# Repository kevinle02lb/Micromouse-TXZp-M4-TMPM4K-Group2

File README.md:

<div align="center">

# 🐭 Toshiba Micromouse

**Autonomous 16×16 Maze-Solving Robot**  
*Register-level firmware on Arm Cortex-M4*

</div>

---

## Overview

Micromouse is a classic robotics competition: an autonomous palm-sized robot explores a 16×16 grid maze, maps the walls, & solves for the center.

This project implements the entire stack from scratch: custom 4-layer PCB, mechanical chassis, and register-level firmware, with no reliance on external HAL libraries.

---

## Platform

<div align="center">

### **Toshiba TMPM4KNF10AFG**, Arm Cortex-M4 with FPU

</div>

The TMPM4KNF10AFG comes from the **[M4K Group](https://toshiba.semicon-storage.com/us/semiconductor/product/microcontrollers/txz4aplus-series/m4k-group.html)** of Toshiba's **[TXZ+™4A Series](https://toshiba.semicon-storage.com/us/semiconductor/product/microcontrollers/txz4aplus-series.html)**, a line of 160 MHz Arm Cortex-M4 microcontrollers built for motor and inverter control. It pairs a fast floating-point core with dedicated on-chip hardware for driving motors, reading encoders, and sampling analog sensors. The same parts show up in BLDC/PMSM drives, HVAC compressors, power tools, and factory automation, and they carry IEC 60730 self-diagnosis support for appliance functional safety.

| Capability | Role in this build |
|-----------|--------------------|
| Cortex-M4 @ 160 MHz + FPU | Navigation, PID, and flood-fill maze solving |
| On-chip motor & encoder hardware | Wheel feedback and PPG-generated motor PWM |
| High-speed analog sensing | IR wall detection |

Here the same silicon runs a much smaller problem: a 1 kHz driven by an interrupt and closed-loop PID over two brushed DC gear-motors. Dedicated hardware handles encoder counting and motor PWM, so the CPU stays free for navigation and flood-fill maze solving.

---

## Built With

<div align="center">

|  |  |  |  |  |  |
|:---:|:---:|:---:|:---:|:---:|:---:|
| **Arm Cortex-M4** | **Keil µVision** | **KiCad** | **Fusion 360** | **Git** | **MATLAB** |
| Register-level C | IDE / Build / Flash | 4-layer PCB | Chassis CAD | Version Control | Data Analysis |

</div>

## Gallery

<div align="center">

 &nbsp;&nbsp;

*Custom PCB*

<br>

*(Outdated Version) Fusion 360 render of the full mechanical assembly*

</div>

---

## Documentation
 
| Path | Contents |
|------|----------|
| [`src/README.md`](src/README.md) | Firmware architecture, control loops, pin map, timer config |
| [`hardware/README.md`](hardware/README.md) | Hardware overview: chassis (Fusion) + PCB (KiCad) |
| [`hardware/pcb/README.md`](hardware/pcb/README.md) | Board specs, layout, schematic, component list |
| [`docs/README.md`](docs/README.md) | Docs index: assets, evidence, and analysis tooling |
| [`docs/evidence/README.md`](docs/evidence/README.md) | Module-test checklist and captured evidence |

---

## Quick Start

```text
IDE:     Keil µVision
Target:  TMPM4KNF10AFG (Arm Cortex-M4)
Debug:   CMSIS-DAP
Flash:   512 KB on-chip

```
[`Quick Start`](docs/README.md)

---

<div align="center">

**Kevin Le** &nbsp;•&nbsp; 2026 &nbsp;
</div>

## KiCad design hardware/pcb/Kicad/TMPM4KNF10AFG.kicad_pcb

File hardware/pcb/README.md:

<div align="center">

# Micromouse PCB

**Custom 4-Layer Control Board**  
*Integrated MCU, motor drivers, and IR sensing*

</div>

---

## Overview

The mainboard is a custom 4-layer PCB designed in KiCad that carries the full electronics stack on a single micromouse-sized board: the microcontroller, dual motor drivers, four IR wall sensors, and the power and debug interface.

---

## Board Specs

| Spec | Detail |
|------|--------|
| Layers | 4-layer |
| MCU | Toshiba TMPM4KNF10AFG (Cortex-M4F) |
| Motor drivers | 2 × TB67H450AFNG H-bridge |
| Sensing | 4 × IR emitter / receiver pairs |
| Debug | CMSIS-DAP (SWD) via TXB0104 level shifter |
| Battery | 3S LiPo, 11.1 V nominal |
| Logic supply | 5 V from a buck converter |

---

## Power

| Rail | Voltage | Source |
|------|---------|--------|
| Battery | 11.1 V (3S LiPo) | Pack |
| Motor | 11.1 V | Direct from pack |
| Logic | 5 V | Buck converter |

Motors are the 12 V variant, so they run straight off the pack. Buck rather than
LDO because 11.1 V down to 5 V is too big a drop to burn as heat.

---

## Layout

<div align="center">

*Copper layers and component placement*

</div>

---

## Key Components

| Component | Part | Role |
|-----------|------|------|
| MCU | TMPM4KNF10AFG | Cortex-M4F, control & sensing |
| Motor driver | TB67H450AFNG ×2 | Brushed DC H-bridge, PWM speed control |
| Motors | Pololu #5211 N20 30:1 | Drive, with quadrature encoders |
| IR sensing | IR LED + phototransistor ×4 | Wall detection via ADC |
| Level shifter | TXB0104 | 5 V ↔ 3.3 V for SWD debug |

---

## Bench Setup

External equipment used for programming and debug:

<div align="center">

 &nbsp;&nbsp; 

*SWD debug via level shifter, and USB-UART for serial logging*

</div>

| Equipment | Purpose |
|-----------|---------|
| CMSIS-DAP probe | SWD programming & debug |
| Logic level shifter | 5 V ↔ 3.3 V for the SWD lines |
| USB-UART converter | Serial console (115200 8-N-1) over the CH340G/debug UART |

Note: TXB0104 OE has a Pull-up. Recommended: 10k - 50k Ohms 

---

## Redesign Notes

Ideas for anyone rebuilding this board, roughly ordered by how much they save.

### Drop to 2 layers

The 4-layer stackup buys a solid ground plane and easy routing. A 2-layer board
runs about half the price at most fabs, and the component count here is low
enough to make it workable. Plan the ground pour carefully around the ADC inputs
if you do.

### Use a 64-pin MCU

The M4K group ships in packages from 64 to 100 pins. This build uses roughly
twenty. A smaller package costs less and frees board area, which is the other
half of shrinking the board.

### Remove the encoder pull-ups

The Pololu encoder board already pulls channels A and B to Vcc through 10 kΩ.
On-board pull-ups parallel those down to 5 kΩ, which works but does nothing
useful. Four resistors saved.

### Hardwire BOOT_N

The bridge connector only matters if you need the built-in serial bootloader.
With SWD programming it never moves, so a 10 kΩ pull-up in its place removes a
connector and an assembly step.

Trade-off: the bootloader is your recovery path if the SWD pins ever get
misconfigured. Losing it means a bad flash is harder to walk back.

### 6 V motors and an LDO

Pololu's 6 V and 12 V HPCB motors perform identically at their own rated
voltages. The 6 V version just draws twice the current. That opens up a 2S pack
with an LDO, dropping 2.4 V instead of 6.1 V, and an LDO is one part rather than
a controller, an inductor, and a capacitor bank.

Trade-off: double the motor current through the H-bridges, and the LDO still runs
warmer than a buck. Cheaper and simpler, not better.

### One dual-channel motor driver

Two single H-bridges could be one dual package. Fewer parts, less area, lower
cost. Check the voltage rating against your pack first, plenty of common dual
drivers top out below a charged 3S.

---

## Schematic

The full schematic is available as a PDF:

[View schematic (PDF)](Schematic.pdf)

---

## Design Files

| File | Contents |
|------|----------|
| [`TMPM4KNF10AFG.kicad_sch`](Kicad/TMPM4KNF10AFG.kicad_sch) | Schematic source (KiCad) |
| [`TMPM4KNF10AFG.kicad_pcb`](Kicad/TMPM4KNF10AFG.kicad_pcb) | Board layout source (KiCad) |
| [`Schematic.pdf`](Schematic.pdf) | Rendered schematic |
| [`board.step`](board.step) | 3D board model (STEP) |
| [`BOM.csv`](BOM.csv) | Bill of materials |
| [`gerber/`](gerber/) | Fabrication outputs |

---

<div align="center">

[← Back to hardware README](../README.md)

</div>

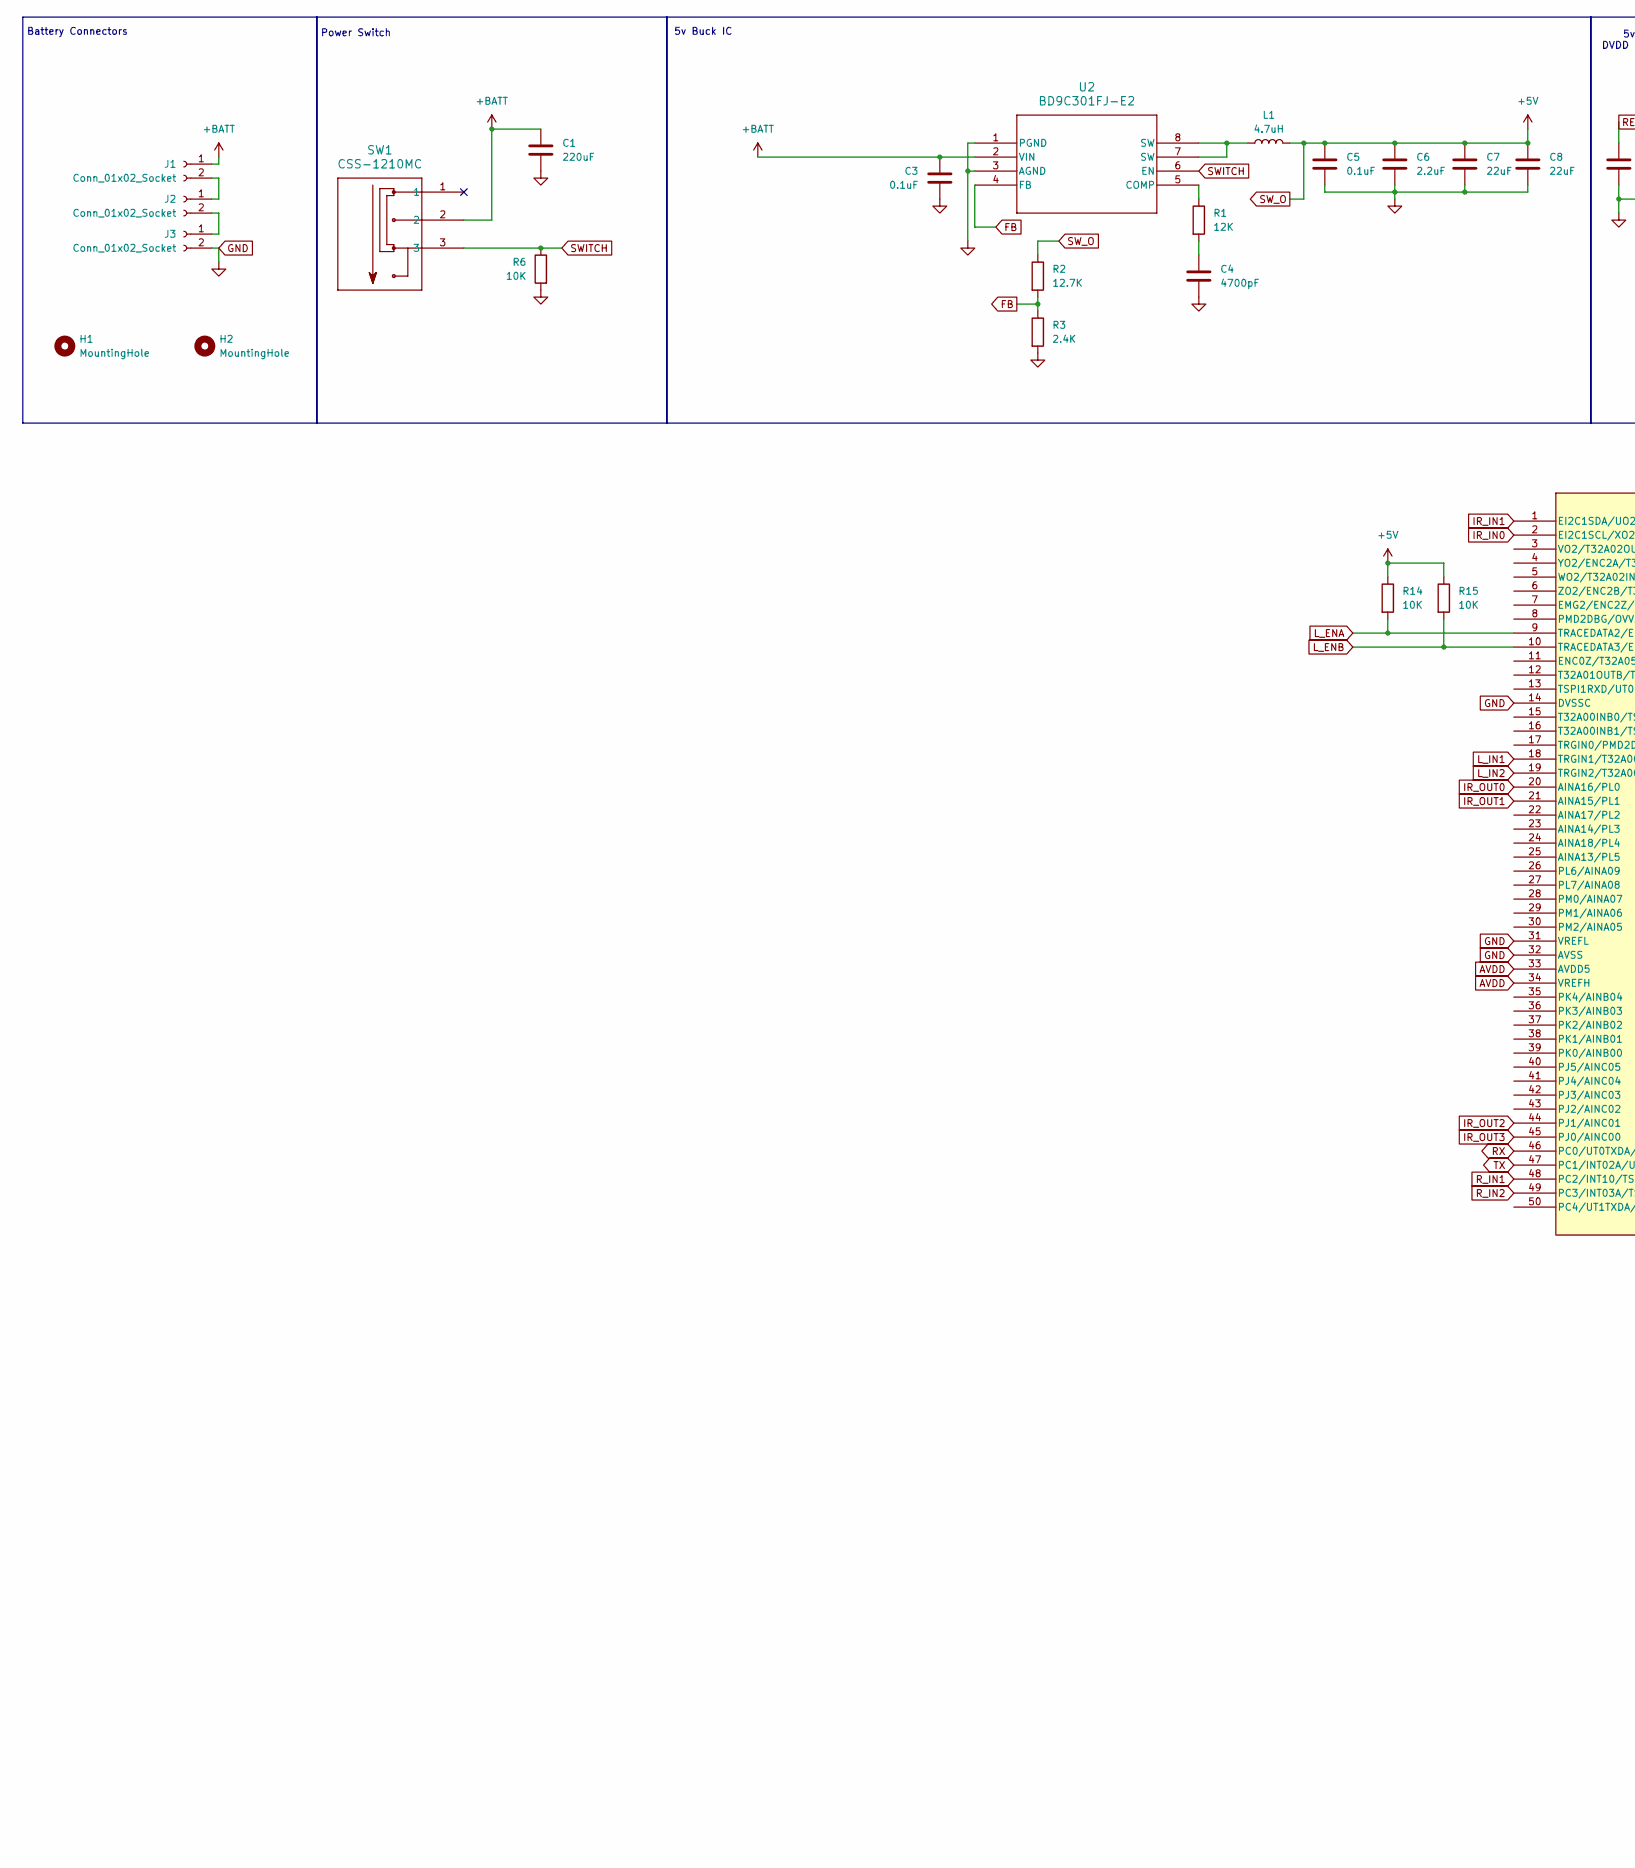
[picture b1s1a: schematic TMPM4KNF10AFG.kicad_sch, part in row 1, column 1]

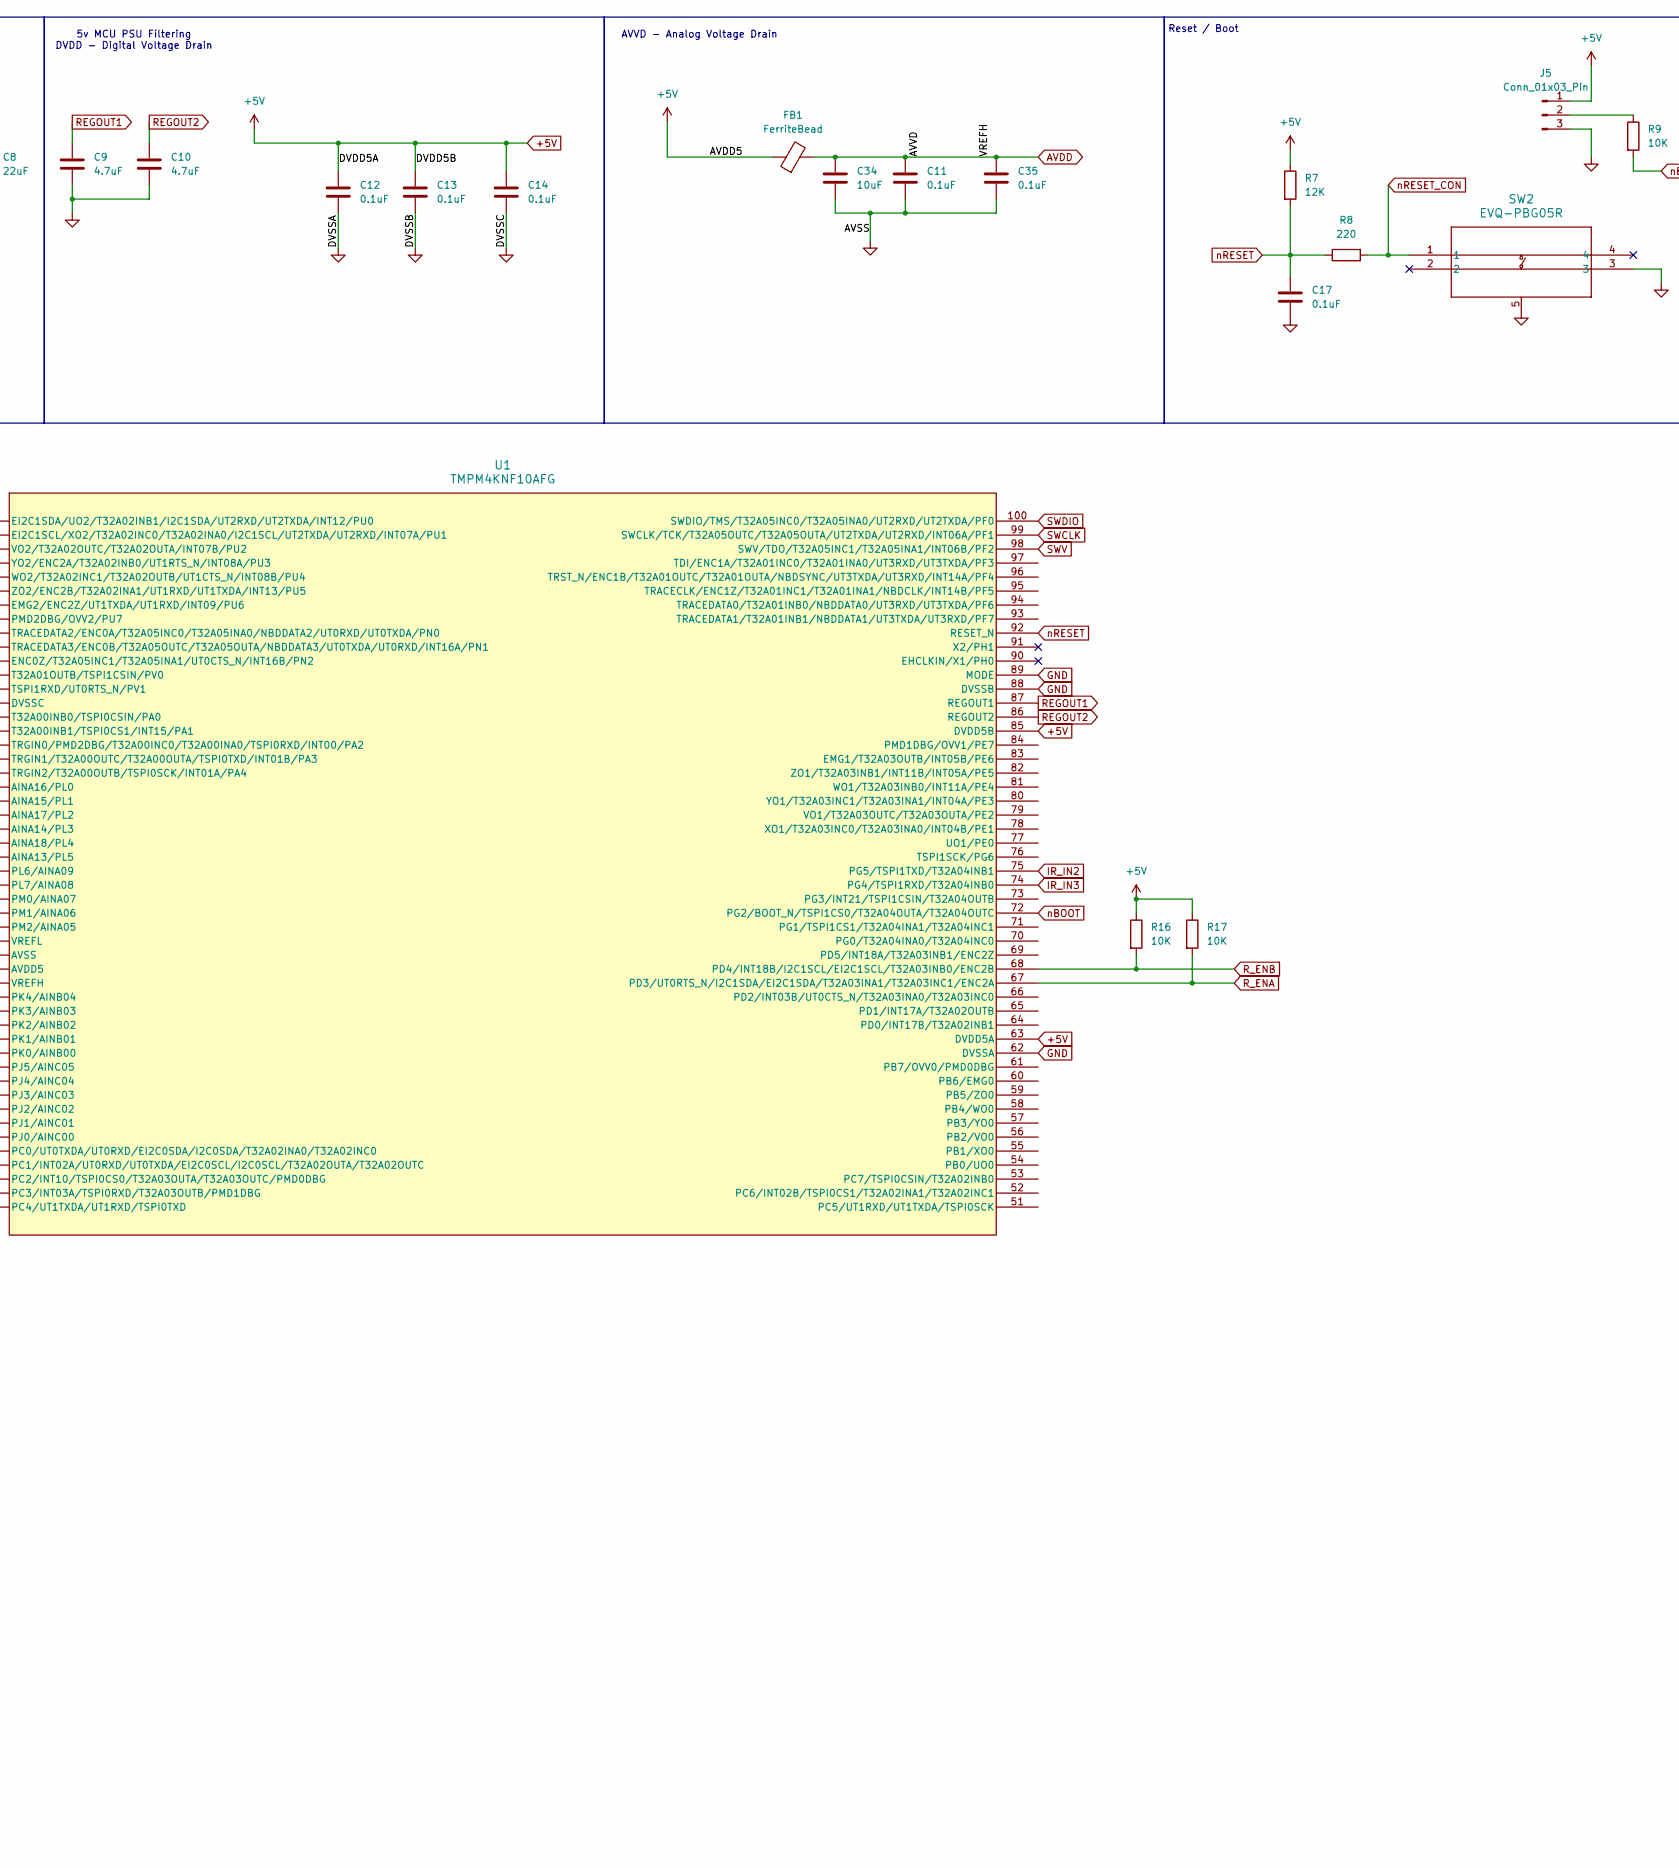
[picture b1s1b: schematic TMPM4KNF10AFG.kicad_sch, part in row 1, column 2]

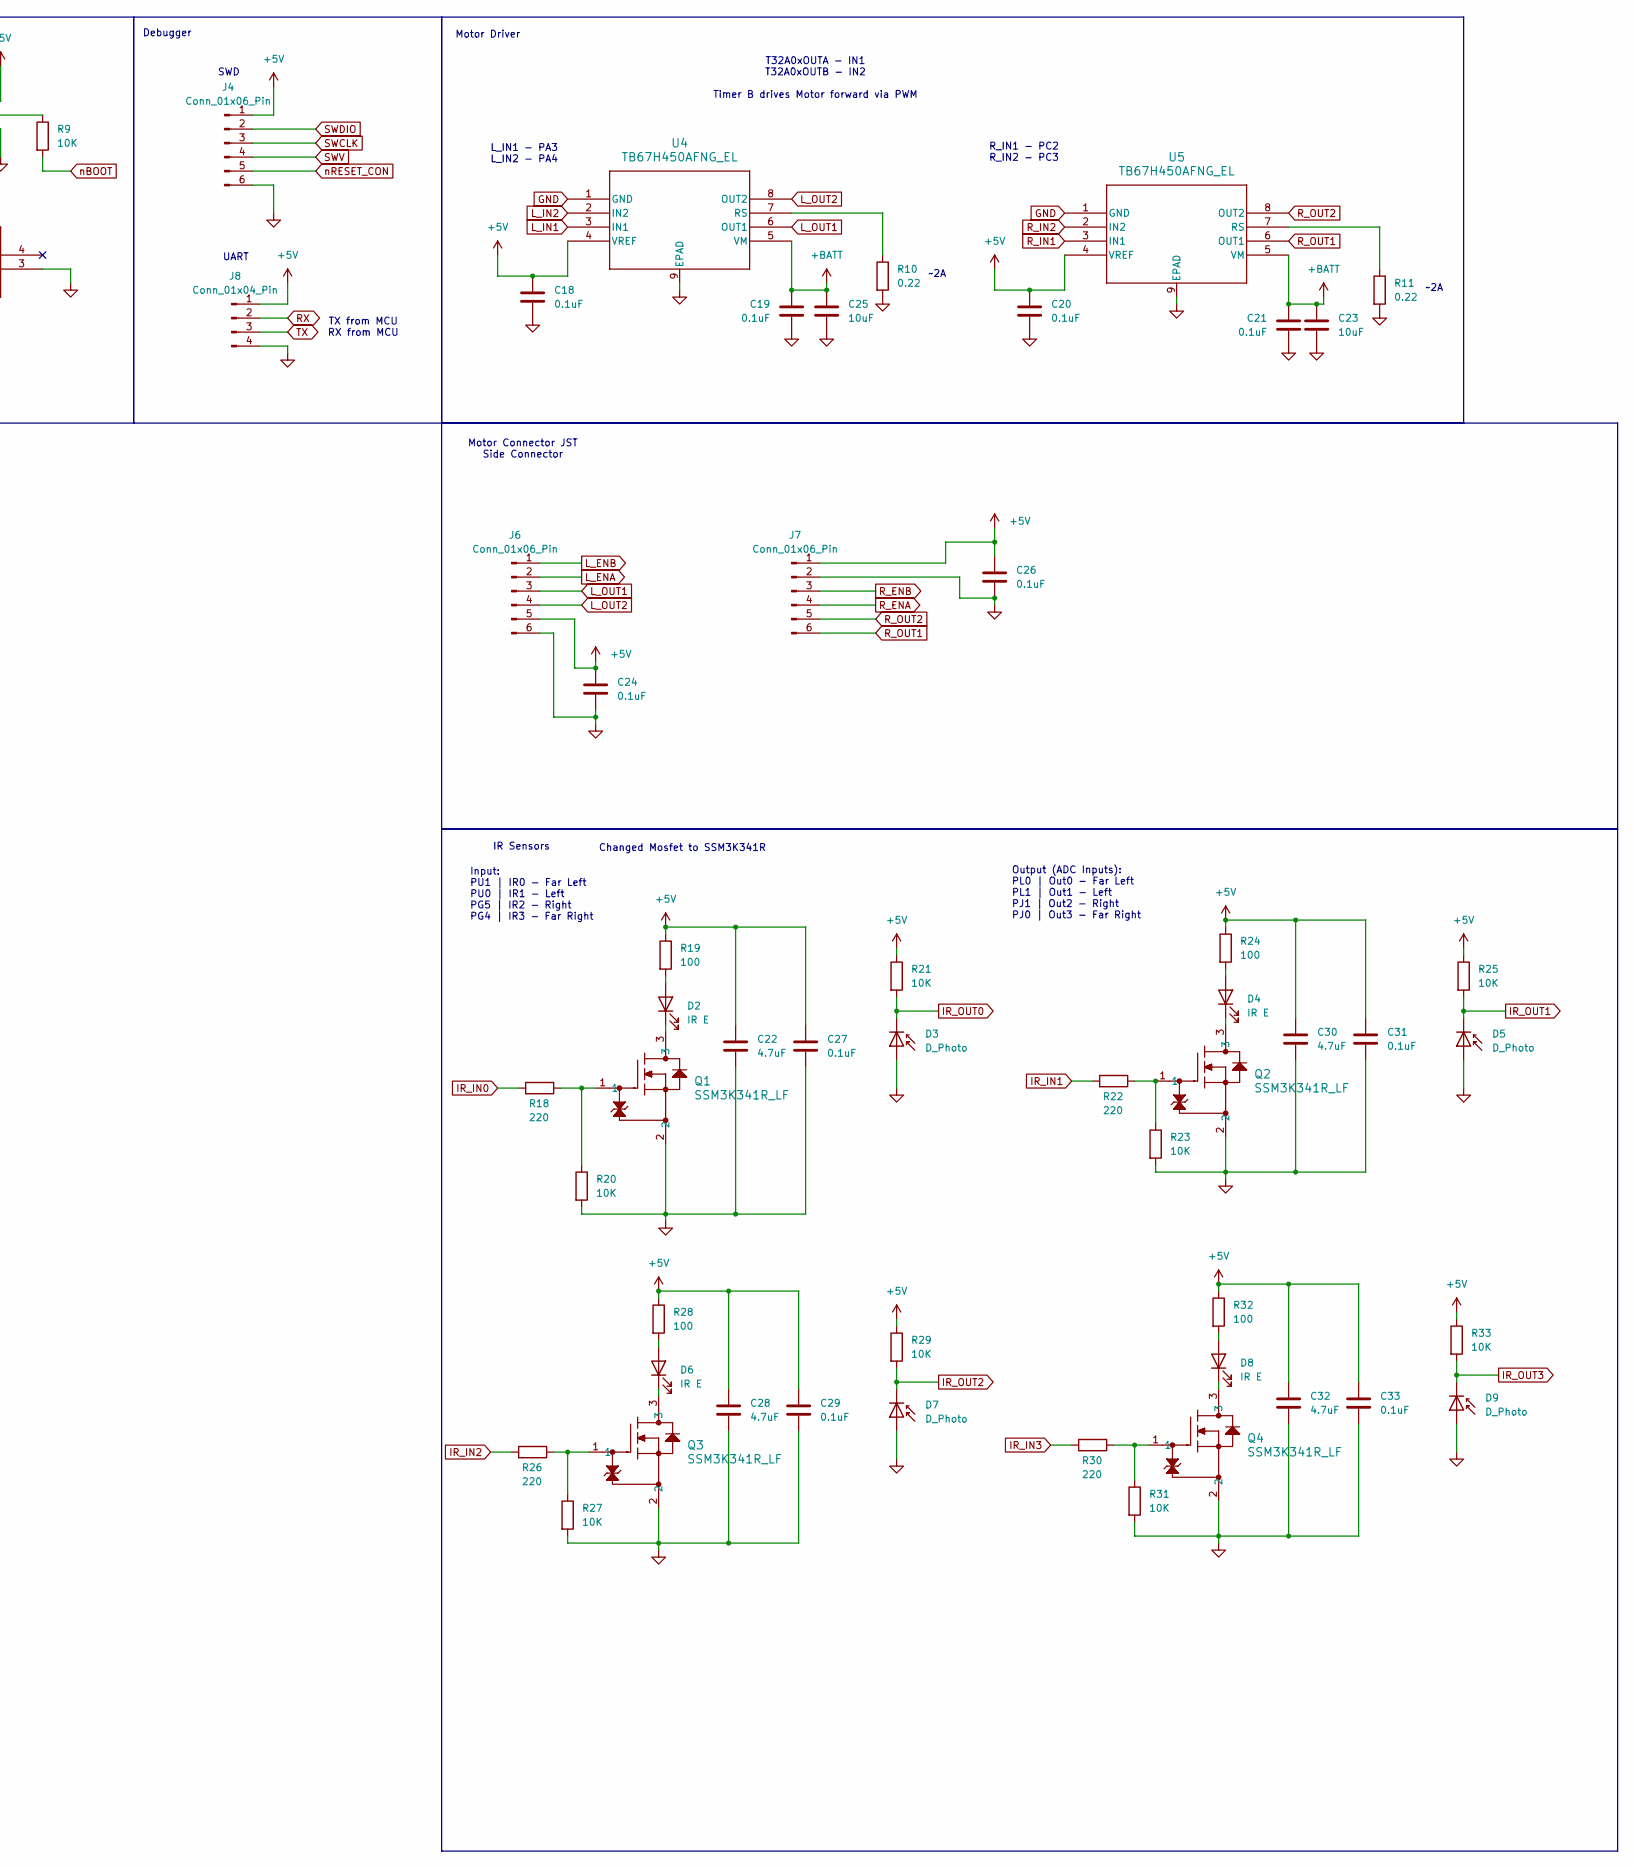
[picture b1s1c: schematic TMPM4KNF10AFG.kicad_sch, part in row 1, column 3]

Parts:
C1: 220uF; CAP_20SVPG220M
C3, C5, C11, C12, C13, C14, C17, C18, C19, C20, C21, C24, C26, C27, C29, C31, C33, C35: 0.1uF; C_0805_2012Metric_Pad1.18x1.45mm_HandSolder
C4: 4700pF; C_0805_2012Metric_Pad1.18x1.45mm_HandSolder
C6: 2.2uF; C_0805_2012Metric_Pad1.18x1.45mm_HandSolder
C7, C8: 22uF; C_0805_2012Metric_Pad1.18x1.45mm_HandSolder
C9, C10, C22, C28, C30, C32: 4.7uF; C_0805_2012Metric_Pad1.18x1.45mm_HandSolder
C23, C25, C34: 10uF; C_0805_2012Metric_Pad1.18x1.45mm_HandSolder
D2, D4, D6, D8: IR E; LED_D5.0mm_Horizontal_O1.27mm_Z3.0mm_Clear
D3, D5, D7, D9: D_Photo; LED_D5.0mm_Horizontal_O1.27mm_Z3.0mm_IRBlack
FB1: FerriteBead; L_0805_2012Metric_Pad1.05x1.20mm_HandSolder
H1, H2: MountingHole; MountingHole_3.2mm_M3
J1, J2, J3: Conn_01x02_Socket; JST_PH_S2B-PH-K_1x02_P2.00mm_Horizontal
J4: Conn_01x06_Pin; PinHeader_1x06_P2.54mm_Vertical
J5: Conn_01x03_Pin; PinHeader_1x03_P2.54mm_Vertical
J6, J7: Conn_01x06_Pin; PAD_01x06_2.54mm
J8: Conn_01x04_Pin; PinHeader_1x04_P2.54mm_Vertical
L1: 4.7uH; IND_1217AS-H-4R7N=P3
Q1, Q2, Q3, Q4: SSM3K341R_LF; SOT-23F_TOS
R1, R7: 12K; R_0805_2012Metric_Pad1.20x1.40mm_HandSolder
R2: 12.7K; R_0805_2012Metric_Pad1.20x1.40mm_HandSolder
R3: 2.4K; R_0805_2012Metric_Pad1.20x1.40mm_HandSolder
R6, R9, R14, R15, R16, R17, R20, R21, R23, R25, R27, R29, R31, R33: 10K; R_0805_2012Metric_Pad1.20x1.40mm_HandSolder
R8, R18, R22, R26, R30: 220; R_0805_2012Metric_Pad1.20x1.40mm_HandSolder
R10, R11: 0.22; R_0805_2012Metric_Pad1.20x1.40mm_HandSolder
R19, R24, R28, R32: 100; R_0805_2012Metric_Pad1.20x1.40mm_HandSolder
SW1: CSS-1210MC; SW3_CSS-1210MC_NDC
SW2: EVQ-PBG05R; EVQ-PBG05R_PAN
U1: TMPM4KNF10AFG; P-LQFP100-1414-0p50-002_TOS
U2: BD9C301FJ-E2; SOP-J8_ROM
U4, U5: TB67H450AFNG_EL; P-HSOP8-0405-1.27-002_TOS

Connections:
+5V: C5.1, C6.1, C7.1, C8.1, C12.1, C13.1, C14.1, C18.1, C20.1, C22.1, C24.1, C26.1, C27.1, C28.1, C29.1, C30.1, C31.1, C32.1, C33.1, FB1.1, J4.1, J5.1, J6.5, J7.1, J8.1, L1.2, R2.1, R7.1, R14.1, R15.1, R16.1, R17.1, R19.1, R21.1, R24.1, R25.1, R28.1, R29.1, R32.1, R33.1, U1.63 (DVDD5A), U1.85 (DVDD5B), U4.4 (VREF), U5.4 (VREF)
+BATT: C1.1, C3.1, C19.1, C21.1, C23.1, C25.1, J1.1, SW1.2, U2.2 (VIN), U4.5 (VM), U5.5 (VM)
AVDD: C11.1, C34.1, C35.1, FB1.2, U1.33 (AVDD5), U1.34 (VREFH)
FB: R2.2, R3.1, U2.4 (FB)
GND: C1.2, C3.2, C4.2, C5.2, C6.2, C7.2, C8.2, C9.2, C10.2, C11.2, C12.2, C13.2, C14.2, C17.2, C18.2, C19.2, C20.2, C21.2, C22.2, C23.2, C24.2, C25.2, C26.2, C27.2, C28.2, C29.2, C30.2, C31.2, C32.2, C33.2, C34.2, C35.2, D3.2 (A), D5.2 (A), D7.2 (A), D9.2 (A), J3.2, J4.6, J5.3, J6.6, J7.2, J8.4, Q1.2, Q2.2, Q3.2, Q4.2, R3.2, R6.2, R10.2, R11.2, R20.2, R23.2, R27.2, R31.2, SW2.3, SW2.5, U1.14 (DVSSC), U1.31 (VREFL), U1.32 (AVSS), U1.62 (DVSSA), U1.88 (DVSSB), U1.89 (MODE), U2.1 (PGND), U2.3 (AGND), U4.1 (GND), U4.9 (EPAD), U5.1 (GND), U5.9 (EPAD)
IR_IN0: R18.2, U1.2 (EI2C1SCL/XO2/T32A02INC0/T32A02INA0/I2C1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)
IR_IN1: R22.2, U1.1 (EI2C1SDA/UO2/T32A02INB1/I2C1SDA/UT2RXD/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)
IR_IN2: R26.2, U1.75 (PG5/TSPI1TXD/T32A04INB1)
IR_IN3: R30.2, U1.74 (PG4/TSPI1RXD/T32A04INB0)
IR_OUT0: D3.1 (K), R21.2, U1.20 (AINA16/PL0)
IR_OUT1: D5.1 (K), R25.2, U1.21 (AINA15/PL1)
IR_OUT2: D7.1 (K), R29.2, U1.44 (PJ1/AINC01)
IR_OUT3: D9.1 (K), R33.2, U1.45 (PJ0/AINC00)
L_ENA: J6.2, R14.2, U1.9 (TRACEDATA2/ENC0A/T32A05INC0/T32A05INA0/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)
L_ENB: J6.1, R15.2, U1.10 (TRACEDATA3/ENC0B/T32A05OUTC/T32A05OUTA/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)
L_IN1: U1.18 (TRGIN1/T32A00OUTC/T32A00OUTA/TSPI0TXD/I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), U4.3 (IN1)
L_IN2: U1.19 (TRGIN2/T32A00OUTB/TSPI0SCK/INT01A/PA4), U4.2 (IN2)
L_OUT1: J6.3, U4.6 (OUT1)
L_OUT2: J6.4, U4.8 (OUT2)
unnamed: C4.1, R1.2
unnamed: D2.2 (A), R19.2
unnamed: D2.1 (K), Q1.3
unnamed: D4.2 (A), R24.2
unnamed: D4.1 (K), Q2.3
unnamed: D6.2 (A), R28.2
unnamed: D6.1 (K), Q3.3
unnamed: D8.2 (A), R32.2
unnamed: D8.1 (K), Q4.3
unnamed: J1.2, J2.1
unnamed: J2.2, J3.1
unnamed: J5.2, R9.1
unnamed: L1.1, U2.7 (SW), U2.8 (SW)
unnamed: Q1.1, R18.1, R20.1
unnamed: Q2.1, R22.1, R23.1
unnamed: Q3.1, R26.1, R27.1
unnamed: Q4.1, R30.1, R31.1
unnamed: R1.1, U2.5 (COMP)
unnamed: R10.1, U4.7 (RS)
unnamed: R11.1, U5.7 (RS)
REGOUT1: C9.1, U1.87 (REGOUT1)
REGOUT2: C10.1, U1.86 (REGOUT2)
RX: J8.2, U1.46 (PC0/UT0TXDA/UT0RXD/EI2C0SDA/I2C0SDA/T32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)
R_ENA: J7.4, R17.2, U1.67 (PD3/UT0RTS_N/I2C1SDA/EI2C1SDA/T32A03INA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)
R_ENB: J7.3, R16.2, U1.68 (PD4/INT18B/I2C1SCL/EI2C1SCL/T32A03INB0/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)
R_IN1: U1.48 (PC2/INT10/TSPI0CS0/T32A03OUTA/T32A03OUT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), U5.3 (IN1)
R_IN2: U1.49 (PC3/INT03A/TSPI0RXD/T32A03OUTB/PMD1DBG), U5.2 (IN2)
R_OUT1: J7.6, U5.6 (OUT1)
R_OUT2: J7.5, U5.8 (OUT2)
SWCLK: J4.3, U1.99 (SWCLK/TCK/T32A05OUTC/T32A05OUTA/UT2TXDA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)
SWDIO: J4.2, U1.100 (SWDIO/TMS/T32A05INC0/T32A05INA0/UT2RXD/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)
SWITCH: R6.1, SW1.3, U2.6 (EN)
SWV: J4.4, U1.98 (SWV/TDO/T32A05INC1/T32A05INA1/INT06B/PF2)
TX: J8.3, U1.47 (PC1/INT02A/UT0RXD/UT0TXDA/EI2C0SCL/I2C0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)
nBOOT: R9.2, U1.72 (PG2/BOOT_N/TSPI1CS0/T32A04OUTA/T32A04OU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)
nRESET: C17.1, R7.2, R8.1, U1.92 (RESET_N)
nRESET_CON: J4.5, R8.2, SW2.1

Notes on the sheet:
Battery Connectors
TX from MCU RX from MCU
R_IN1 - PC2 R_IN2 - PC3
Motor Connector JST Side Connector
Changed Mosfet to SSM3K341R
UART
Output (ADC Inputs): PL0 | Out0 - Far Left PL1 | Out1 - Left PJ1 | Out2 - Right PJ0 | Out3 - Far Right
5v MCU PSU Filtering DVDD - Digital Voltage Drain
IR Sensors
T32A0xOUTA - IN1 T32A0xOUTB - IN2 Timer B drives Motor forward via PWM
Power Switch
Debugger
5v Buck IC
~2A
L_IN1 - PA3 L_IN2 - PA4
Motor Driver
SWD
AVVD - Analog Voltage Drain
Input: PU1 | IR0 - Far Left PU0 | IR1 - Left PG5 | IR2 - Right PG4 | IR3 - Far Right
Reset / Boot

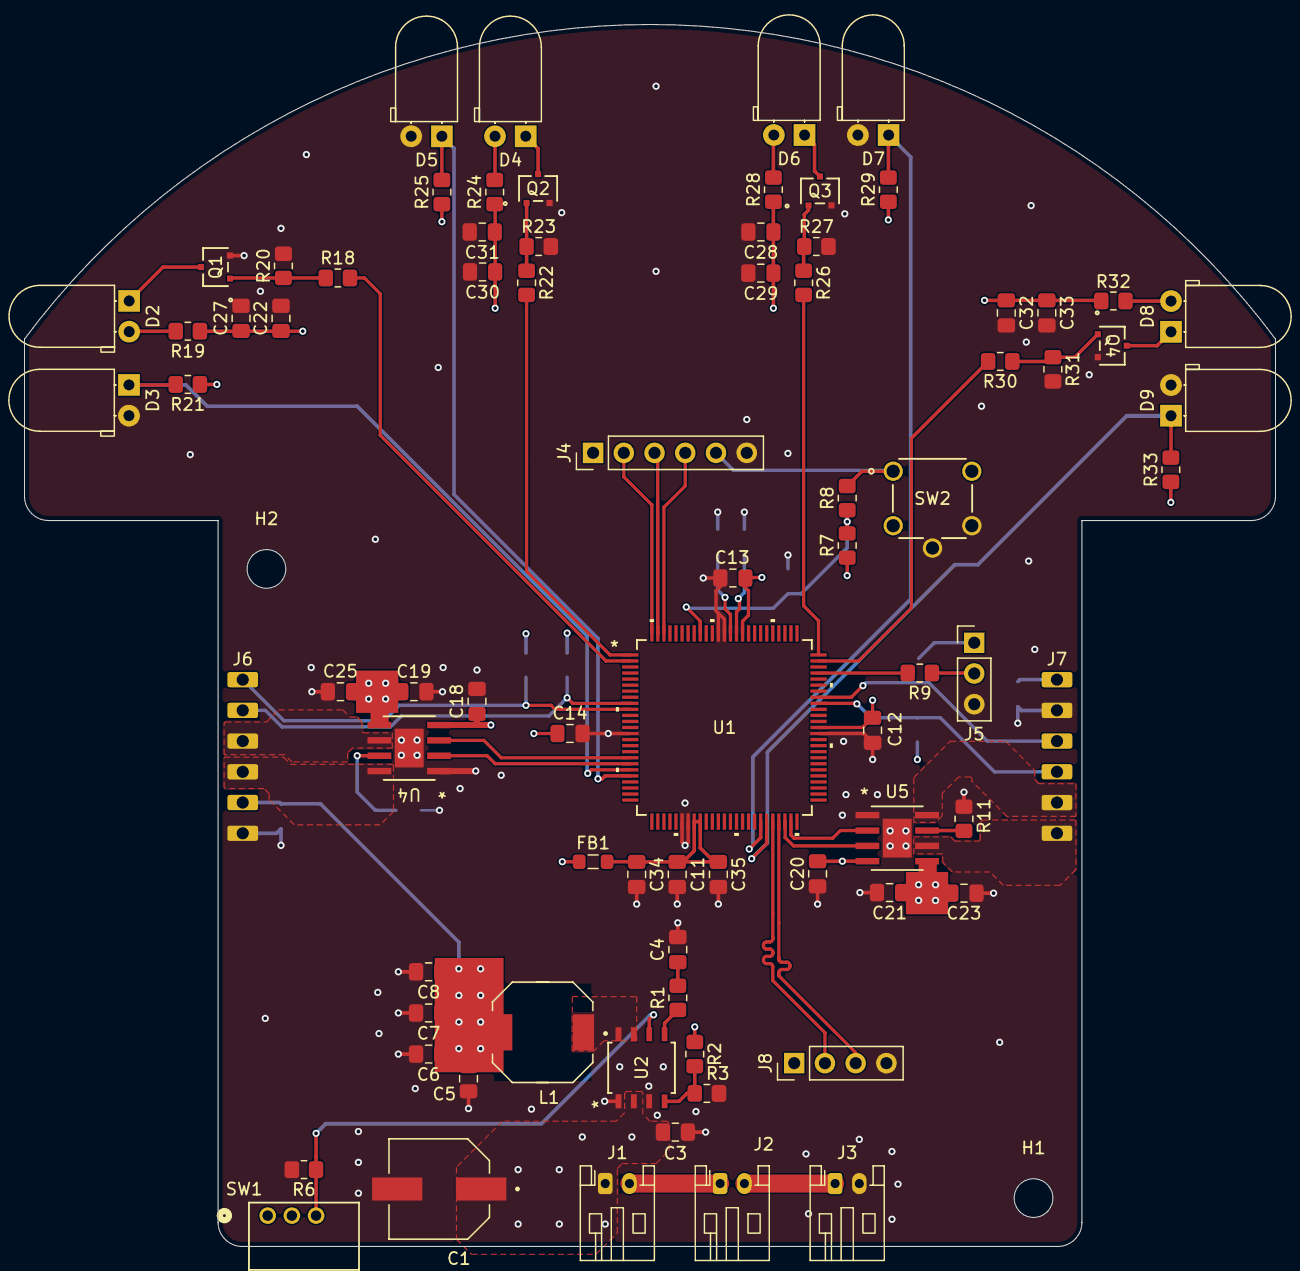
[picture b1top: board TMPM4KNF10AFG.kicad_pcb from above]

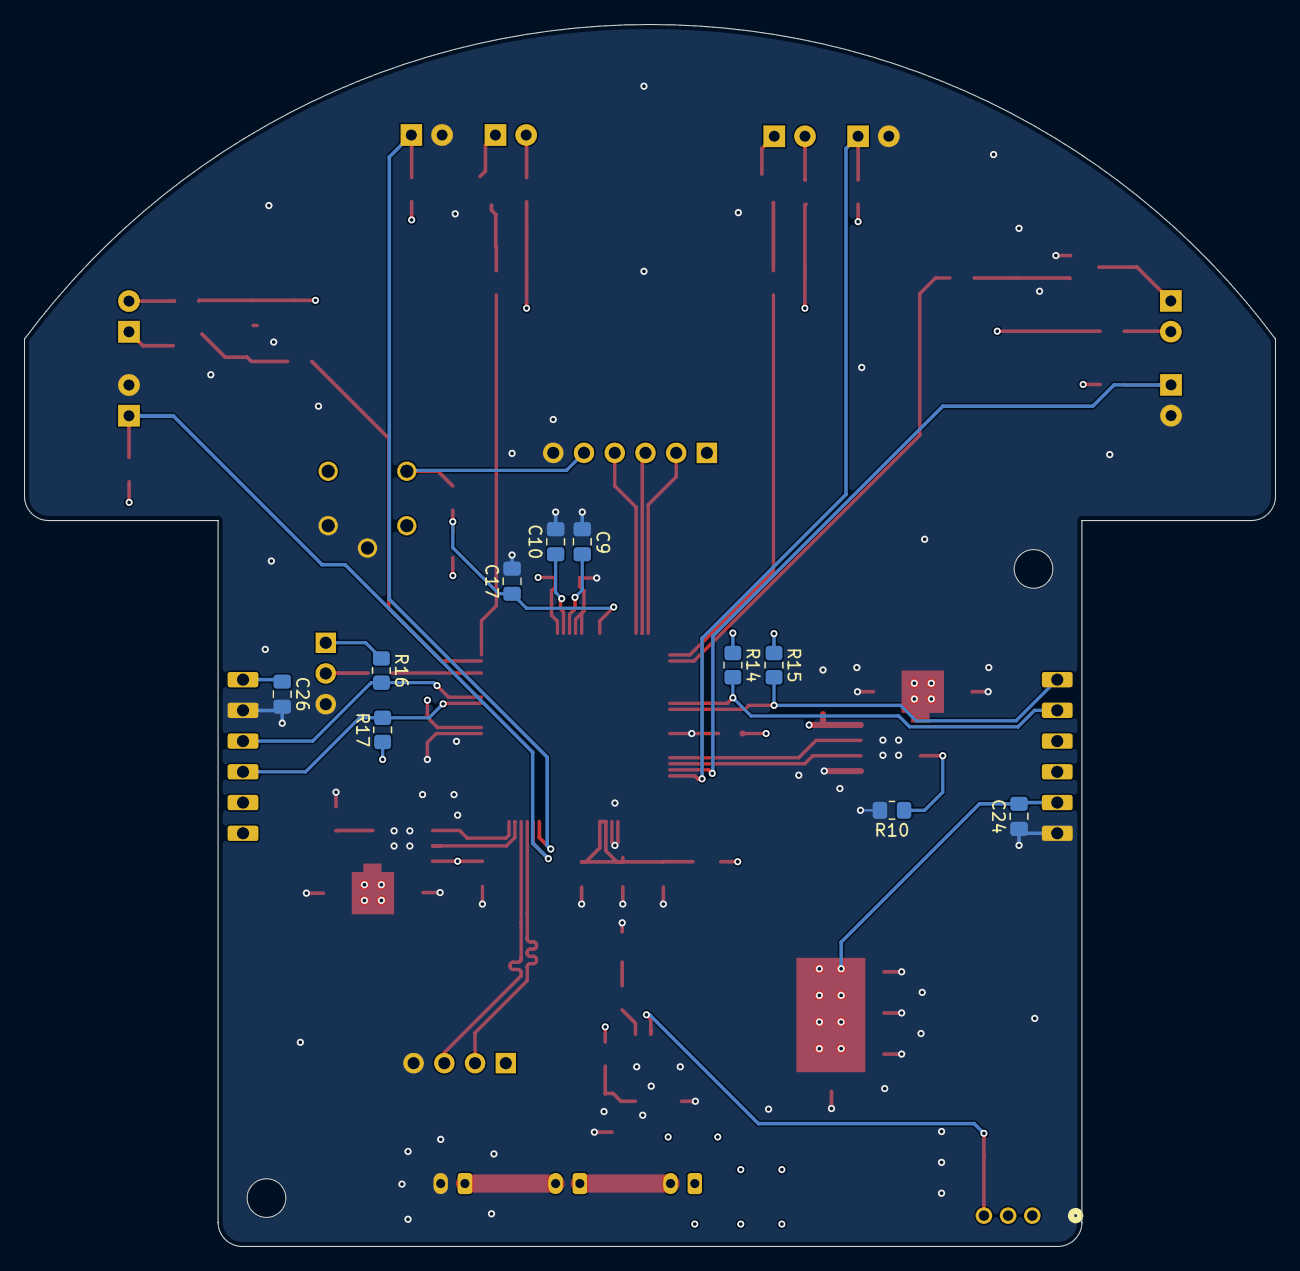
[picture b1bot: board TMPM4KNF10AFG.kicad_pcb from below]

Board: 4 copper layers, 103.4 x 101.0 mm, 91 parts (10 on the bottom side), 56 nets.

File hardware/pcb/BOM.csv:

"Reference","Qty","Value","DNP","Exclude from BOM","Exclude from Board","Footprint","Datasheet"
"U4,U5","2","TB67H450AFNG_EL","","","","TB67H450AFNG:P-HSOP8-0405-1.27-002_TOS","TB67H450AFNG_EL"
"U2","1","BD9C301FJ-E2","","","","BD9C301FJ:SOP-J8_ROM","https://fscdn.rohm.com/en/products/databook/datasheet/ic/pow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"
"U1","1","TMPM4KNF10AFG","","","","TMPM4KNF10AFG:P-LQFP100-1414-0p50-002_TOS","TMPM4KNF10AFG"
"SW2","1","EVQ-PBG05R","","","","EVQ-PBG05R:EVQ-PBG05R_PAN","EVQ-PBG05R"
"SW1","1","CSS-1210MC","","","","CSS-1210MC:SW3_CSS-1210MC_NDC","CSS-1210MC"
"R19,R24,R28,R32","4","100","","","","Resistor_SMD:R_0805_2012Metric_Pad1.20x1.40mm_HandSolder",""
"R10,R11","2","0.22","","","","Resistor_SMD:R_0805_2012Metric_Pad1.20x1.40mm_HandSolder",""
"R6,R9,R14,R15,R16,R17,R20,R21,R23,R25,R27,R29,R31,R33","14","10K","","","","Resistor_SMD:R_0805_2012Metric_Pad1.20x1.40mm_HandSolder","https://industrial.panasonic.com/cdbs/www-data/pdf/RDM0000/A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"
"R5,R8,R18,R22,R26,R30","6","220","","","","Resistor_SMD:R_0805_2012Metric_Pad1.20x1.40mm_HandSolder","https://industrial.panasonic.com/cdbs/www-data/pdf/RDM0000/A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"
"R4","1","1K","","","","Resistor_SMD:R_0805_2012Metric_Pad1.20x1.40mm_HandSolder",""
"R3","1","2.4K","","","","Resistor_SMD:R_0805_2012Metric_Pad1.20x1.40mm_HandSolder",""
"R2","1","12.7K","","","","Resistor_SMD:R_0805_2012Metric_Pad1.20x1.40mm_HandSolder",""
"R1,R7","2","12K","","","","Resistor_SMD:R_0805_2012Metric_Pad1.20x1.40mm_HandSolder",""
"Q1,Q2,Q3,Q4,Q5","5","NMOS","","","","SSM3K324R,LF:SOT-23F_TOS-M","https://toshiba.semicon-storage.com/info/SSM3K324R_datasheet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"
"L1","1","4.7uH","","","","1217AS-H-4R7N=P3:IND_1217AS-H-4R7N=P3","https://www.murata.com/~/media/webrenewal/products/inductor/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"
"J8","1","Conn_01x04_Pin","","","","Connector_PinHeader_2.54mm:PinHeader_1x04_P2.54mm_Vertical",""
"J6,J7","2","Conn_01x06_Pin","","","","Library:PAD_01x06_2.54mm",""
"J5","1","Conn_01x03_Pin","","","","Connector_PinHeader_2.54mm:PinHeader_1x03_P2.54mm_Vertical",""
"J4","1","Conn_01x06_Pin","","","","Connector_PinHeader_2.54mm:PinHeader_1x06_P2.54mm_Vertical",""
"J1,J2,J3","3","Conn_01x02_Socket","","","","Connector_JST:JST_PH_S2B-PH-K_1x02_P2.00mm_Horizontal",""
"FB1","1","FerriteBead","","","","Inductor_SMD:L_0805_2012Metric_Pad1.05x1.20mm_HandSolder","https://pim.murata.com/asset/pim4/ferriteBeadInductortypefil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"
"D3,D5,D7,D9","4","IR R","","","","LED_THT:LED_D5.0mm_Horizontal_O1.27mm_Z3.0mm_IRBlack",""
"D2,D4,D6,D8","4","IR E","","","","LED_THT:LED_D5.0mm_Horizontal_O1.27mm_Z3.0mm_Clear",""
"D1","1","CRZ10","DNP","","","Diode_SMD:D_SOD-123F","https://toshiba.semicon-storage.com/info/CRY68_datasheet_en_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"
"C23,C25,C34","3","10uF","","","","Capacitor_SMD:C_0805_2012Metric_Pad1.18x1.45mm_HandSolder","https://search.murata.co.jp/Ceramy/image/img/A01X/G101/ENG/G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"
"C9,C10,C22,C28,C30,C32","6","4.7uF","","","","Capacitor_SMD:C_0805_2012Metric_Pad1.18x1.45mm_HandSolder",""
"C7,C8","2","22uF","","","","Capacitor_SMD:C_0805_2012Metric_Pad1.18x1.45mm_HandSolder","https://search.murata.co.jp/Ceramy/image/img/A01X/G101/ENG/G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"
"C6","1","2.2uF","","","","Capacitor_SMD:C_0805_2012Metric_Pad1.18x1.45mm_HandSolder","https://search.murata.co.jp/Ceramy/image/img/A01X/G101/ENG/G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"
"C4","1","4700pF","","","","Capacitor_SMD:C_0805_2012Metric_Pad1.18x1.45mm_HandSolder",""
"C3,C5,C11,C12,C13,C14,C17,C18,C19,C20,C21,C24,C26,C27,C29,C31,C33,C35","18","0.1uF","","","","Capacitor_SMD:C_0805_2012Metric_Pad1.18x1.45mm_HandSolder","https://search.murata.co.jp/Ceramy/image/img/A01X/G101/ENG/G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,https://search.murata.co.jp/Ceramy/image/img/A01X/G101/ENG/G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"
"C1,C2","2","220uF","","","","20SVPG220M:CAP_20SVPG220M","https://mm.digikey.com/Volume0/opasdata/d220001/medias/docus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"

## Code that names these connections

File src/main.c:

/**
 ******************************************************************************
 * @file        main.c
 * @brief       Micromouse main firmware entry point
 * @version     V1.0.0
 * @date        05-05-2026
 *
 * @details
 *   Initializes the system clock and all modules, then runs the main control
 *   loop. Every 1 kHz tick (T32A1 interval timer) runs the full pipeline in
 *   fixed order:
 *
 *     Encoder_Update()   -> read quadrature counters, filter wheel speed
 *     Odometry_Update()  -> integrate pose (x, y, heading) from encoders
 *     Motion_Update()    -> PID speed loop, drive motor PWM (ALWAYS runs)
 *     Navigator_Update() -> non-blocking FSM: plan -> turn -> drive -> pause
 *
 *   Navigator is the top-level brain: it calls FloodFill (pure planner) for
 *   the next move, then sequences the physical turn/drive without ever
 *   blocking, so the PID loop above keeps running every tick.
 *
 *   Deployment calibration (must set before real runs):
 *   - IrSensor.c : ir_cal[] table (measured ADC-to-distance points)
 *   - Odometry.h : WHEELBASE_MM (measure wheel-center to wheel-center)
 *   - Encoder    : confirm forward motion yields INCREASING position
 *   - PID.h      : tune gains for CPS-scaled error
 *
 * ___________________________________________________________________________
 * Hardware:
 *   - MCU:     TMPM4KNF10AFG (ARM Cortex-M4, 5V, 160 MHz)
 *   - Motors:  TB67H450AFNG x2 + Pololu #5211 N20 30:1
 *   - Sensors: IR emitter/receiver pairs x4
 *   - Debug:   External CMSIS-DAP w/ Level Shifter (TXB0104)
 *
 * ___________________________________________________________________________
 * Pin Assignment:
 *   ┌─────────────────────────────────────────────────────────────┐
 *   │  PORT A  │ PA3  = 	 T32A00OUTA  (Left PWM IN1)            │
 *   │          │ PA4  = 	 T32A00OUTB  (Left PWM IN2)            │
 *   ├─────────────────────────────────────────────────────────────┤
 *   │  PORT C  │ PC2  = 	 T32A30OUTA  (Right PWM IN1)           │
 *   │          │ PC3  = 	 T32A30OUTB  (Right PWM IN2)           │
 *   ├─────────────────────────────────────────────────────────────┤
 *   │  PORT N  │ PN0  = 	 ENC0A  (Left encoder A)               │
 *   │          │ PN1  = 	 ENC0B  (Left encoder B)               │
 *   ├─────────────────────────────────────────────────────────────┤
 *   │  PORT D  │ PD3  = 	 ENC2A  (Right encoder A)              │
 *   │          │ PD4  = 	 ENC2B  (Right encoder B)              │
 *   ├─────────────────────────────────────────────────────────────┤
 *   │  PORT L  │ PL0  = 	 AINA16  (Far Left IR)                 │
 *   │          │ PL1  = 	 AINA15  (Left IR)                     │
 *   ├─────────────────────────────────────────────────────────────┤
 *   │  PORT J  │ PJ0  =     AINC00  (Far Right IR)                │
 *   │          │ PJ1  = 	 AINC01  (Right IR)                    │
 *   ├─────────────────────────────────────────────────────────────┤
 *   │  PORT U  │ PU0  =     Left IR Emitter                       │
 *   │          │ PU1  =     Far Left IR Emitter                   │
 *   ├─────────────────────────────────────────────────────────────┤
 *   │  PORT G  │ PG4  =     Far Right IR Emitter                  │
 *   │          │ PG5  =     Right IR Emitter                      │
 *   └─────────────────────────────────────────────────────────────┘
 *
 * ___________________________________________________________________________
 * Aliases (for quick reference):
 *   - PA3 = IN1, PA4 = IN2  (Left motor, T32A00OUTA/B)
 *   - PC2 = IN1, PC3 = IN2  (Right motor, T32A30OUTA/B)
 *   - PN0 = ENC0A, PN1 = ENC0B  (Left encoder)
 *   - PD3 = ENC2A, PD4 = ENC2B  (Right encoder)
 *   - PL0 = AINA16 (Far Left IR), PL1 = AINA15 (Left IR)
 *   - PJ1 = AINC01 (Right IR), PJ0 = AINC00 (Far Right IR)
 *   - PU1 = Far Left IR Emitter, PU0 = Left IR Emitter
 *   - PG5 = Right IR Emitter, PG4 = Far Right IR Emitter
 *
 * ___________________________________________________________________________
 * Notes:
 *   - MCU must be powered at 5V for ADC to function.
 *   - See TMPM4KNF10AFG datasheet section 7.2.
 *
 * ___________________________________________________________________________
 * References:
 *   - Product Info:  https://toshiba.semicon-storage.com/info/TXZP-PINFO-M4K(2)_en_20231225.pdf?did=70854
 *   - Datasheet:     https://toshiba.semicon-storage.com/info/TMPM4KNF10AFG_datasheet_en_20250516.pdf?did=155921&prodName=TMPM4KNF10AFG
 *
 * Copyright (c) [Kevin Le] 2026
 ******************************************************************************
 */


/* Inclusions */
#include "TMPM4KyA.h"
#include "system_TMPM4KyA.h"
#include "modules/Timebase.h"    // 1 kHz tick flag (T32A1)
#include "modules/Encoder.h"     // quadrature speed + position
#include "modules/Odometry.h"    // pose estimate (x, y, heading)
#include "modules/Motion.h"      // PID speed loop + motor drive
#include "modules/IrSensor.h"    // IR wall sensing (ADC)
#include "modules/FloodFill.h"   // pure maze planner (BFS)
#include "modules/Navigator.h"   // top-level motion sequencer FSM
#include "drivers/uart.h"		 // uart for debugging


void ModuleInit(void);




int main(void)
{
	SystemInit();								/* Initialize system clock and peripherals */
	ModuleInit();
	

	/* Control loop: fires once per 1 kHz tick. Order matters — each stage
	 * consumes the output of the one above it within the same tick.       */
	while (1)
	{
		if (Timebase_GetAndClear())     // true once per 1 ms tick
		{
			Encoder_Update();       // 1. read encoders, filter speed
			Odometry_Update();      // 2. update pose from encoders
			IR_SampleStep();        // 3. sample IR readings
			Navigator_Update();     // 4. plan/turn/drive FSM step
			Motion_Update();        // 5. PID -> motor PWM
		}
	}

	return 0;
}



/**
 * @brief  Initialize all modules in dependency order.
 * @note   Call once after SystemInit().
 *
 *   Each driver configures its own GPIO port internally, so no separate
 *   GPIO_Init() pass is needed. SysTick needs no init (stateless).
 *
 *   Order:
 *   1. Motion   -> Encoder + Motor (PWM T32A0/3, encoder ports) up first
 *   2. Odometry -> caches encoder position, so must follow Motion
 *   3. IR       -> ADC + emitter ports; ADC uses SysTick_us (stateless)
 *   4. FloodFill-> planner; samples IR on first Plan(), so IR must precede it
 *   5. Navigator-> depends on FloodFill + Motion
 *   6. Timebase -> starts 1 kHz tick LAST
 */
void ModuleInit(void)
{
    Motion_Init();      // -> Encoder_Init() + Motor_Init()
    Odometry_Init();    // reads Encoder position
    IR_Init();          // ADC_Init() + emitter ports
    FloodFill_Init();
    Navigator_Init();
    Timebase_Init();    // start tick last
}

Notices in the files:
README.md:
License: MIT
